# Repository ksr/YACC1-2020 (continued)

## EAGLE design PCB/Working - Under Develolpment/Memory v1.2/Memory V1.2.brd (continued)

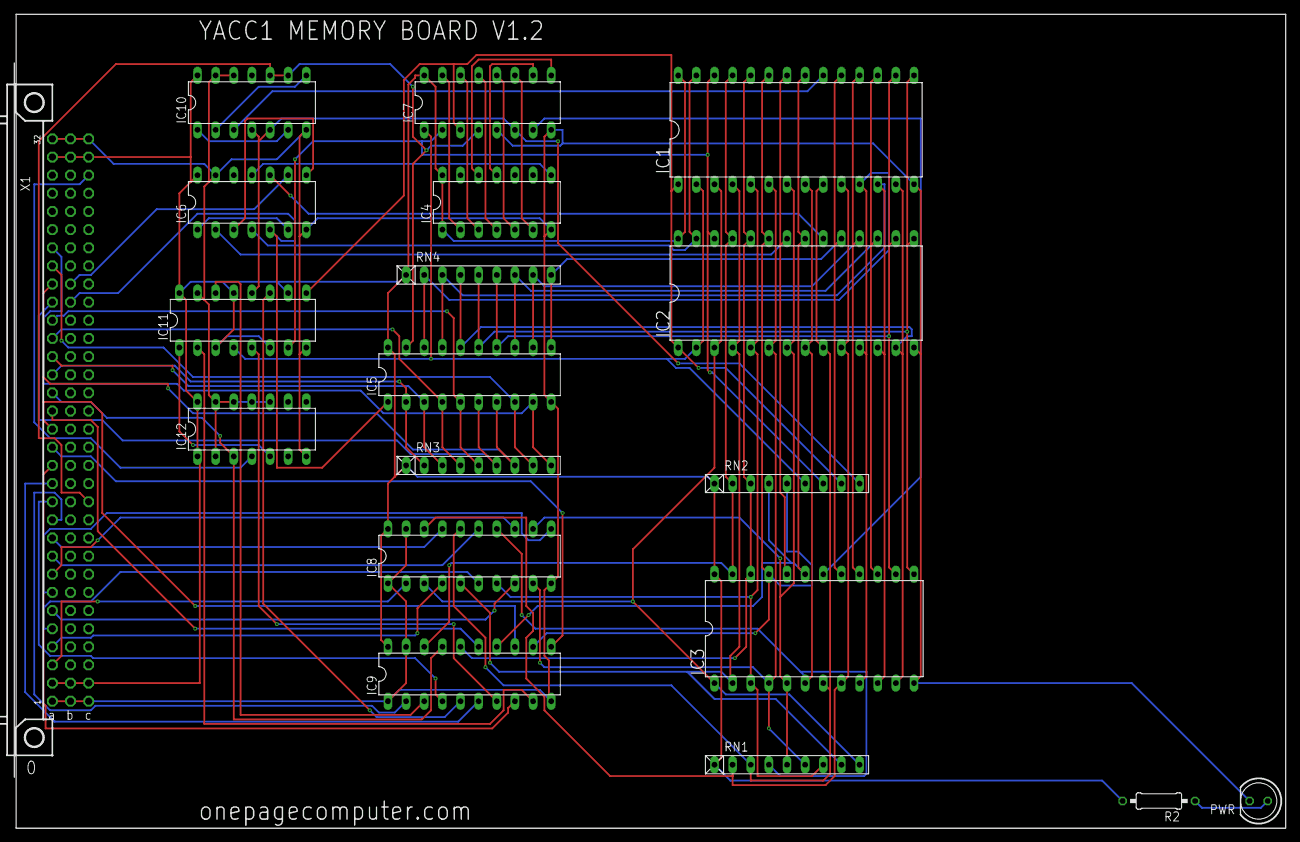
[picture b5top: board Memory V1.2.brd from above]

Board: 2 copper layers, 177.8 x 114.0 mm, 19 parts (0 on the bottom side), 77 nets.

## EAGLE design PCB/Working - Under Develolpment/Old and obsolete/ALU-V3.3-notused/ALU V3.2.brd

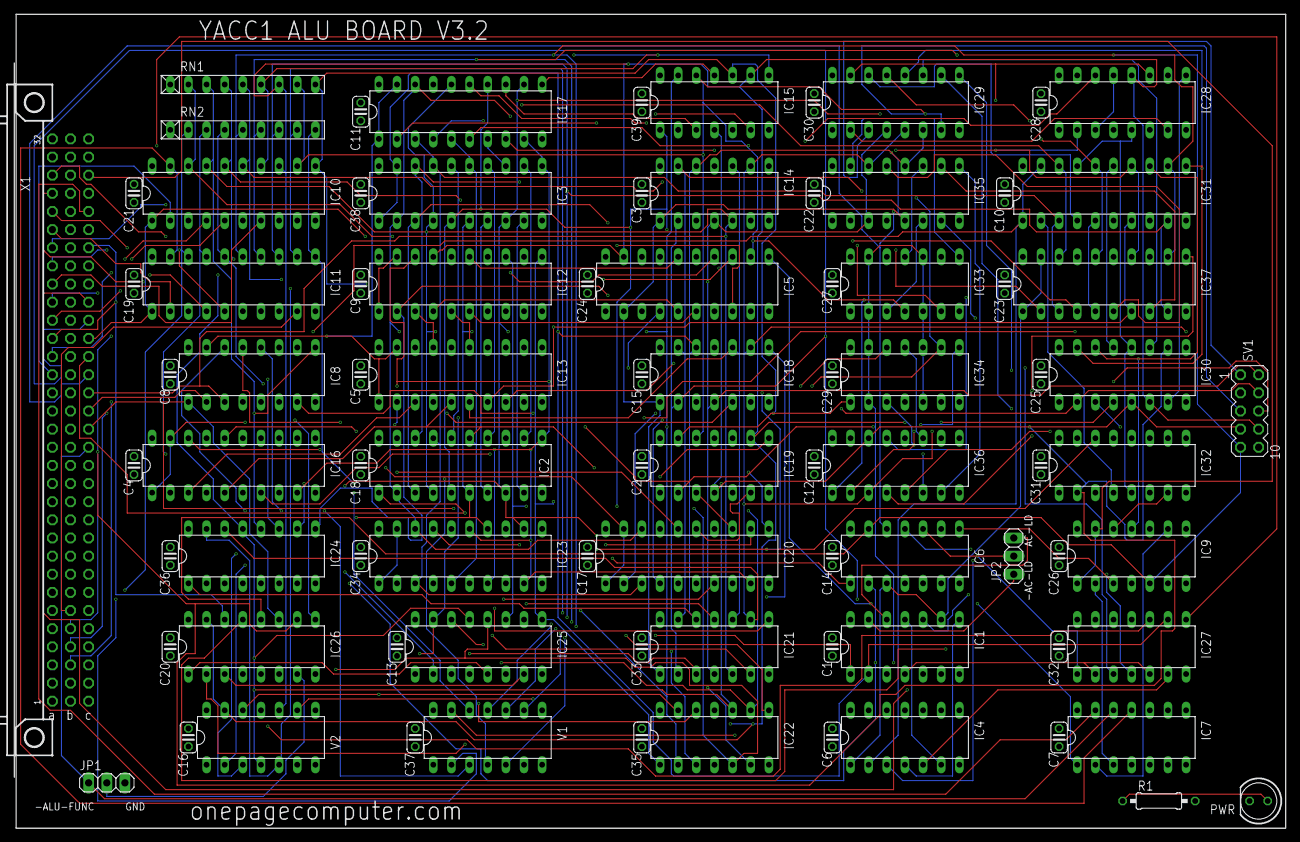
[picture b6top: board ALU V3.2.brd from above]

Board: 4 copper layers, 177.8 x 114.0 mm, 86 parts (0 on the bottom side), 162 nets.

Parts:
C1, C2, C3, C4, C5, C6, C7, C8, C9, C10, C11, C12, C13, C14, C15, C16, C17, C18, C19, C20, C22, C23, C24, C25, C26, C27, C28, C29, C30, C31, C32, C33, C34, C35, C36, C37, C38, C39: .1uf; C025-024X044
C21: ,1uf; C025-024X044
IC1: 74ALS04N; DIL14
IC2: 74LS240N; DIL20
IC3, IC12, IC13, IC16, IC17, IC20, IC23, IC31, IC37: 74LS244N; DIL20
IC4: 74LS00N; DIL14
IC5: 74LS374N; DIL20
IC6: 74ALS08N; DIL14
IC7, IC21, IC22: 74LS32N; DIL14
IC8: 74LS138N; DIL16
IC9: 74LS74N; DIL14
IC10, IC11: 74LS245N; DIL20
IC14, IC15, IC27, IC33, IC34: 74LS86N; DIL14
IC18, IC19: 74LS08N; DIL14
IC24, IC25: 74LS85N; DIL16
IC26: 74LS251N; DIL16
IC28, IC32: 74LS153N; DIL16
IC29, IC30: 74LS194N; DIL16
IC35, IC36: 74LS283N; DIL16
JP1, JP2: 1X03
PWR: LED5MM
R1: 330; 0207/10
RN1, RN2: 10k; RN-9
SV1: MA05-2
V1, V2: 744078N; DIL14
X1: FABC96R

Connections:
-AC-LD: IC1.13, JP2.1, X1.C22
-AC-LD-INV: IC1.1, IC2.1, IC2.19, X1.C20
-AC-RD: IC10.1, IC11.1, IC12.1, IC12.19, X1.C21
-ADD: IC6.1, IC8.7
-ADD/SUB: IC1.9, IC4.1, IC6.3, IC37.1, IC37.19
-ALU-FUNC: IC7.12, JP1.1, X1.C15
-ALU-IO-EN: IC7.11, IC10.19, IC11.19
-AND: IC8.13, IC20.1, IC20.19
-BUS-EN: IC7.13, X1.C28
-DATA: IC8.15, IC13.1, IC13.19
-OR: IC8.12, IC23.1, IC23.19
-RESET: IC9.1, IC9.13, X1.C30
-SHIFT: IC4.2, IC8.10, IC31.1, IC31.19
-SR-LD: IC1.5, X1.C23
-SUB: IC1.3, IC6.2, IC8.14
-XOR: IC8.11, IC17.1, IC17.19
-ZERO: IC8.9, IC16.1, IC16.19
AC-LD: IC1.12, IC5.11, JP2.3
AC-LD-INV: IC1.2, IC3.1, IC3.19, IC27.9
ACI-DATA0: IC2.18, IC3.18, IC5.3
ACI-DATA1: IC2.16, IC3.16, IC5.4
ACI-DATA2: IC2.14, IC3.14, IC5.7
ACI-DATA3: IC2.12, IC3.12, IC5.8
ACI-DATA4: IC2.9, IC3.9, IC5.13
ACI-DATA5: IC2.7, IC3.7, IC5.14
ACI-DATA6: IC2.5, IC3.5, IC5.17
ACI-DATA7: IC2.3, IC3.3, IC5.18
ACO-DATA0: IC5.2, IC12.2, IC14.1, IC18.1, IC21.1, IC24.9, IC29.3, IC35.5, SV1.1
ACO-DATA1: IC5.5, IC12.4, IC14.4, IC18.4, IC21.4, IC24.11, IC29.4, IC35.3, SV1.2
ACO-DATA2: IC5.6, IC12.6, IC14.9, IC18.9, IC21.9, IC24.14, IC29.5, IC35.14, SV1.3
ACO-DATA3: IC5.9, IC12.8, IC14.12, IC18.12, IC21.12, IC24.1, IC29.6, IC30.2, IC35.12, SV1.4
ACO-DATA4: IC5.12, IC12.11, IC15.12, IC19.12, IC22.1, IC25.9, IC29.7, IC30.3, IC36.5, SV1.5
ACO-DATA5: IC5.15, IC12.13, IC15.1, IC19.1, IC22.4, IC25.11, IC30.4, IC36.3, SV1.6
ACO-DATA6: IC5.16, IC12.15, IC15.4, IC19.4, IC22.9, IC25.14, IC30.5, IC36.14, SV1.7
ACO-DATA7: IC5.19, IC12.17, IC15.9, IC19.9, IC22.12, IC25.1, IC28.12, IC30.6, IC36.12, SV1.8
ALU0: IC8.1, IC26.11, IC29.9, IC30.9, IC32.14, X1.C16
ALU1: IC8.2, IC26.10, IC29.10, IC30.10, IC32.2, X1.C17
ALU2: IC8.3, IC26.9, IC28.14, X1.C18
ALU3: IC6.12, IC28.2, X1.C19
BDATA0: IC10.18, IC12.18, IC13.2, IC14.2, IC18.2, IC21.2, IC24.10, IC33.1, RN1.2, V2.2
BDATA1: IC10.17, IC12.16, IC13.4, IC14.5, IC18.5, IC21.5, IC24.12, IC33.4, RN1.3, V2.3
BDATA2: IC10.16, IC12.14, IC13.6, IC14.10, IC18.10, IC21.10, IC24.13, IC33.9, RN1.4, V2.4
BDATA3: IC10.15, IC12.12, IC13.8, IC14.13, IC18.13, IC21.13, IC24.15, IC33.12, RN1.5, V2.5
BDATA4: IC10.14, IC12.9, IC13.11, IC15.13, IC19.13, IC22.2, IC25.10, IC34.1, RN1.6, V2.9
BDATA5: IC10.13, IC12.7, IC13.13, IC15.2, IC19.2, IC22.5, IC25.12, IC34.4, RN1.7, V2.10
BDATA6: IC10.12, IC12.5, IC13.15, IC15.5, IC19.5, IC22.10, IC25.13, IC34.9, RN1.8, V2.11
BDATA7: IC10.11, IC12.3, IC13.17, IC15.10, IC19.10, IC22.13, IC25.15, IC34.12, RN1.9, V2.12
BDATA8: IC11.18, RN2.2, V1.2
BDATA9: IC11.17, RN2.3, V1.3
BDATA10: IC11.16, RN2.4, V1.4
BDATA11: IC11.15, RN2.5, V1.5
BDATA12: IC11.14, RN2.6, V1.9
BDATA13: IC11.13, RN2.7, V1.10
BDATA14: IC11.12, RN2.8, V1.11
BDATA15: IC11.11, RN2.9, V1.12
BR-COND: IC27.8, X1.C24
C/SHIFT: IC6.13, IC9.5, IC26.12, IC28.3, IC28.13, SV1.9
CO/BO: IC1.10, IC7.1
DATA0: IC10.2, X1.A19
DATA1: IC10.3, X1.A20
DATA2: IC10.4, X1.A21
DATA3: IC10.5, X1.A22
DATA4: IC10.6, X1.A23
DATA5: IC10.7, X1.A24
DATA6: IC10.8, X1.A25
DATA7: IC10.9, X1.A26
DATA8: IC11.2, X1.A27
DATA9: IC11.3, X1.A28
DATA10: IC11.4, X1.A29
DATA11: IC11.5, X1.A30
DATA12: IC11.6, X1.B3
DATA13: IC11.7, X1.B4
DATA14: IC11.8, X1.B5
DATA15: IC11.9, X1.B6
GND: C1.2, C2.2, C3.2, C4.2, C5.2, C6.2, C7.2, C8.2, C9.2, C10.2, C11.2, C12.2, C13.2, C14.2, C15.2, C16.2, C17.2, C18.2, C19.2, C20.2, C21.2, C22.2, C23.2, C24.2, C25.2, C26.2, C27.2, C28.2, C29.2, C30.2, C31.2, C32.2, C33.2, C34.2, C35.2, C36.2, C37.2, C38.2, C39.2, IC1.7, IC2.10, IC3.10, IC4.7, IC4.9, IC4.10, IC4.12, IC4.13, IC5.1, IC5.10, IC6.7, IC7.4, IC7.5, IC7.7, IC7.9, IC7.10, IC8.4, IC8.5, IC8.8, IC9.7, IC10.10, IC11.10, IC12.10, IC13.10, IC14.7, IC15.7, IC16.2, IC16.4, IC16.6, IC16.8, IC16.10, IC16.11, IC16.13, IC16.15, IC16.17, IC17.10, IC18.7, IC19.7, IC20.10, IC21.7, IC22.7, IC23.10, IC24.2, IC24.4, IC24.8, IC25.8, IC26.8, IC27.7, IC27.12, IC27.13, IC28.1, IC28.4, IC28.6, IC28.8, IC28.10, IC28.15, IC29.8, IC30.8, IC31.10, IC32.1, IC32.3, IC32.6, IC32.8, IC32.10, IC32.11, IC32.12, IC32.13, IC32.15, IC33.7, IC34.7, IC35.8, IC36.8, IC37.10, JP1.3, PWR.K, SV1.10, V1.7, V2.7, X1.A1, X1.A32, X1.B1, X1.B32, X1.C1, X1.C32
IN: IC26.14, X1.C26
INV-IN0: IC2.2, IC3.2, IC13.18, IC16.18, IC17.18, IC20.18, IC23.18, IC31.18, IC37.18
INV-IN1: IC2.4, IC3.4, IC13.16, IC16.16, IC17.16, IC20.16, IC23.16, IC31.16, IC37.16
INV-IN2: IC2.6, IC3.6, IC13.14, IC16.14, IC17.14, IC20.14, IC23.14, IC31.14, IC37.14
INV-IN3: IC2.8, IC3.8, IC13.12, IC16.12, IC17.12, IC20.12, IC23.12, IC31.12, IC37.12
INV-IN4: IC2.11, IC3.11, IC13.9, IC16.9, IC17.9, IC20.9, IC23.9, IC31.9, IC37.9
INV-IN5: IC2.13, IC3.13, IC13.7, IC16.7, IC17.7, IC20.7, IC23.7, IC31.7, IC37.7
INV-IN6: IC2.15, IC3.15, IC13.5, IC16.5, IC17.5, IC20.5, IC23.5, IC31.5, IC37.5
INV-IN7: IC2.17, IC3.17, IC13.3, IC16.3, IC17.3, IC20.3, IC23.3, IC31.3, IC37.3
unnamed: IC27.4, IC36.9
unnamed: IC27.3, IC35.7
unnamed: IC4.3, IC6.9
unnamed: IC26.7, JP1.2
unnamed: IC6.8, IC9.3
unnamed: IC6.4, IC26.15, V2.13
unnamed: IC7.3, IC9.2
unnamed: IC6.11, IC27.1
unnamed: IC6.10, JP2.2
unnamed: IC4.5, IC27.6
unnamed: IC9.12, IC32.7
unnamed: IC33.6, IC35.2
unnamed: IC34.6, IC36.2
unnamed: PWR.A, R1.1
unnamed: IC1.8, IC4.4
unnamed: IC1.11, IC4.6
unnamed: IC33.8, IC35.15
unnamed: IC33.11, IC35.11
unnamed: IC33.3, IC35.6
unnamed: IC34.3, IC36.6
unnamed: IC34.8, IC36.15
unnamed: IC34.11, IC36.11
unnamed: IC35.4, IC37.2
unnamed: IC35.1, IC37.4
unnamed: IC35.13, IC37.6
unnamed: IC35.10, IC37.8
unnamed: IC36.4, IC37.11
unnamed: IC36.1, IC37.13
unnamed: IC36.13, IC37.15
unnamed: IC36.10, IC37.17
unnamed: IC35.9, IC36.7
unnamed: IC24.5, IC25.4
unnamed: IC24.6, IC25.3
unnamed: IC24.7, IC25.2
unnamed: IC25.7, IC26.3
unnamed: IC25.6, IC26.2
unnamed: IC25.5, IC26.1
unnamed: IC6.5, V1.13
unnamed: IC6.6, IC26.13
unnamed: IC26.5, IC27.10
unnamed: IC29.14, IC31.4
unnamed: IC29.13, IC31.6
unnamed: IC29.12, IC31.8
unnamed: IC30.15, IC31.11
unnamed: IC30.14, IC31.13
unnamed: IC30.13, IC31.15
unnamed: IC28.7, IC29.2
unnamed: IC28.9, IC30.7
unnamed: IC21.3, IC23.2
unnamed: IC21.6, IC23.4
unnamed: IC21.8, IC23.6
unnamed: IC21.11, IC23.8
unnamed: IC22.3, IC23.11
unnamed: IC22.6, IC23.13
unnamed: IC22.8, IC23.15
unnamed: IC22.11, IC23.17
unnamed: IC18.3, IC20.2
unnamed: IC18.6, IC20.4
unnamed: IC18.8, IC20.6
unnamed: IC18.11, IC20.8
unnamed: IC19.11, IC20.11
unnamed: IC19.3, IC20.13
unnamed: IC19.6, IC20.15
unnamed: IC19.8, IC20.17
unnamed: IC14.3, IC17.2
unnamed: IC14.6, IC17.4
unnamed: IC14.8, IC17.6
unnamed: IC14.11, IC17.8
unnamed: IC15.11, IC17.11
unnamed: IC15.3, IC17.13
unnamed: IC15.6, IC17.15
unnamed: IC15.8, IC17.17
SHIFT-OUT: IC7.2, IC9.9
SR-LD: IC1.6, IC9.11, IC29.11, IC30.11
SRD0: IC28.11, IC29.15, IC31.2, IC32.4
SRD7: IC28.5, IC30.12, IC31.17, IC32.5
SUB: IC1.4, IC27.2, IC27.5, IC33.2, IC33.5, IC33.10, IC33.13, IC34.2, IC34.5, IC34.10, IC34.13
VCC: C1.1, C2.1, C3.1, C4.1, C5.1, C6.1, C7.1, C8.1, C9.1, C10.1, C11.1, C12.1, C13.1, C14.1, C15.1, C16.1, C17.1, C18.1, C19.1, C20.1, C21.1, C22.1, C23.1, C24.1, C25.1, C26.1, C27.1, C28.1, C29.1, C30.1, C31.1, C32.1, C33.1, C34.1, C35.1, C36.1, C37.1, C38.1, C39.1, IC1.14, IC2.20, IC3.20, IC4.14, IC5.20, IC6.14, IC7.14, IC8.6, IC8.16, IC9.4, IC9.10, IC9.14, IC10.20, IC11.20, IC12.20, IC13.20, IC14.14, IC15.14, IC16.20, IC17.20, IC18.14, IC19.14, IC20.20, IC21.14, IC22.14, IC23.20, IC24.3, IC24.16, IC25.16, IC26.4, IC26.16, IC27.14, IC28.16, IC29.1, IC29.16, IC30.1, IC30.16, IC31.20, IC32.16, IC33.14, IC34.14, IC35.16, IC36.16, IC37.20, R1.2, RN1.1, RN2.1, V1.14, V2.14, X1.A2, X1.A31, X1.B2, X1.B31, X1.C2, X1.C31

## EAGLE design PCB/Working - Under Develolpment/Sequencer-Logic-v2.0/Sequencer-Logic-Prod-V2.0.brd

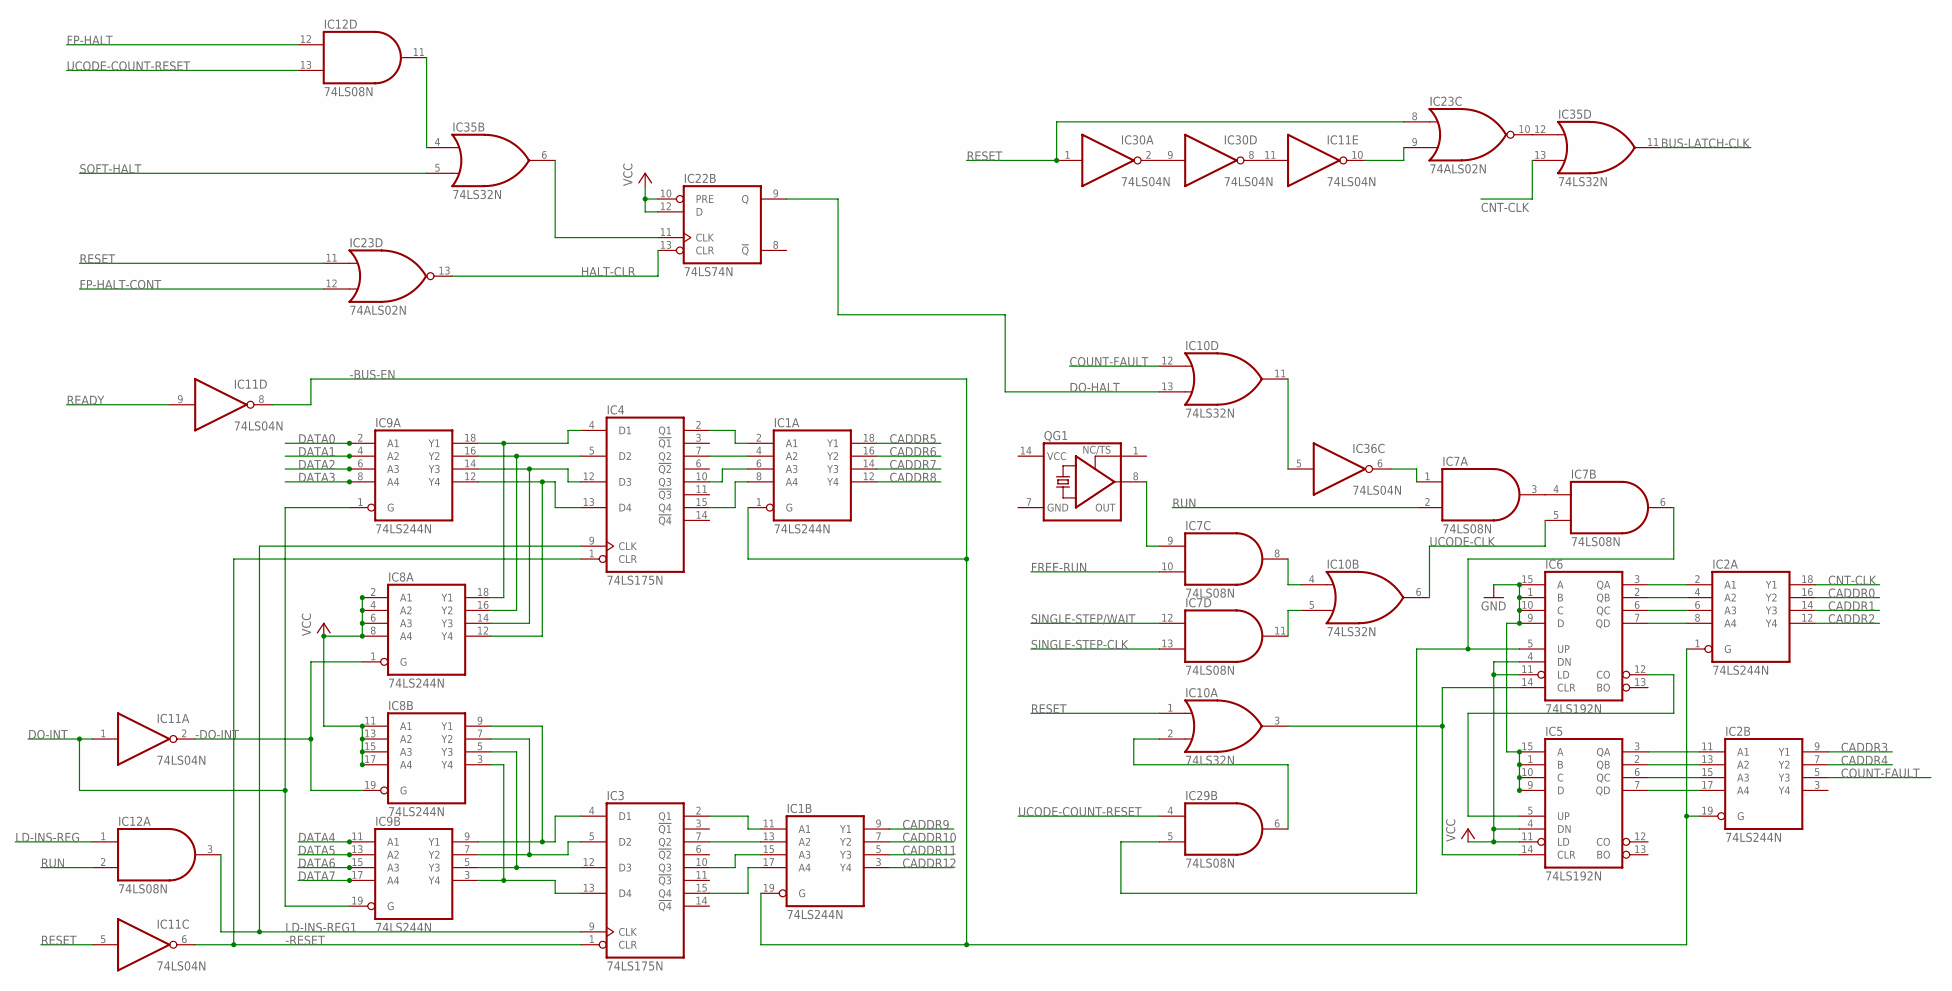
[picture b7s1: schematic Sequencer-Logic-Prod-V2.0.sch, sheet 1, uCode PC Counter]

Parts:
IC1, IC2, IC8, IC9: 74LS244N; DIL20
IC3, IC4: 74LS175N; DIL16
IC5, IC6: 74LS192N; DIL16
IC7, IC12, IC29: 74LS08N; DIL14
IC10, IC35: 74LS32N; DIL14
IC11, IC30, IC36: 74LS04N; DIL14
IC22: 74LS74N; DIL14
IC23: 74ALS02N; DIL14
QG1: XO-14; DIL14S

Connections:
-BUS-EN: IC1.1 (G), IC1.19 (G), IC2.1 (G), IC2.19 (G), IC11.8 (O); also elsewhere on the board
-DO-INT: IC8.1 (G), IC8.19 (G), IC11.2 (O)
-RESET: IC3.1 (CLR), IC4.1 (CLR), IC11.6 (O); also elsewhere on the board
BUS-LATCH-CLK: IC35.11 (O); also elsewhere on the board
CADDR0: IC2.16 (Y2); also elsewhere on the board
CADDR1: IC2.14 (Y3); also elsewhere on the board
CADDR2: IC2.12 (Y4); also elsewhere on the board
CADDR3: IC2.9 (Y1); also elsewhere on the board
CADDR4: IC2.7 (Y2); also elsewhere on the board
CADDR5: IC1.18 (Y1); also elsewhere on the board
CADDR6: IC1.16 (Y2); also elsewhere on the board
CADDR7: IC1.14 (Y3); also elsewhere on the board
CADDR8: IC1.12 (Y4); also elsewhere on the board
CADDR9: IC1.9 (Y1); also elsewhere on the board
CADDR10: IC1.7 (Y2); also elsewhere on the board
CADDR11: IC1.5 (Y3); also elsewhere on the board
CADDR12: IC1.3 (Y4); also elsewhere on the board
CNT-CLK: IC2.18 (Y1), IC35.13 (I1)
COUNT-FAULT: IC2.5 (Y3), IC10.12 (I0)
COUNT-RESET: IC5.14 (CLR), IC6.14 (CLR), IC10.3 (O)
DATA0: IC9.2 (A1); also elsewhere on the board
DATA1: IC9.4 (A2); also elsewhere on the board
DATA2: IC9.6 (A3); also elsewhere on the board
DATA3: IC9.8 (A4); also elsewhere on the board
DATA4: IC9.11 (A1); also elsewhere on the board
DATA5: IC9.13 (A2); also elsewhere on the board
DATA6: IC9.15 (A3); also elsewhere on the board
DATA7: IC9.17 (A4); also elsewhere on the board
DO-HALT: IC10.13 (I1), IC22.9 (Q)
DO-INT: IC9.1 (G), IC9.19 (G), IC11.1 (I); also elsewhere on the board
FP-HALT: IC12.12 (I0); also elsewhere on the board
FP-HALT-CONT: IC23.12 (I1); also elsewhere on the board
FREE-RUN: IC7.10 (I1); also elsewhere on the board
GND: IC1.10 (GND), IC2.10 (GND), IC3.8 (GND), IC4.8 (GND), IC5.1 (B), IC5.8 (GND), IC5.9 (D), IC5.10 (C), IC5.15 (A), IC6.1 (B), IC6.8 (GND), IC6.9 (D), IC6.10 (C), IC6.15 (A), IC7.7 (GND), IC8.10 (GND), IC9.10 (GND), IC10.7 (GND), IC11.7 (GND), IC12.7 (GND), IC22.7 (GND), IC23.7 (GND), IC29.7 (GND), IC30.7 (GND), IC35.7 (GND), IC36.7 (GND), QG1.7 (GND); also elsewhere on the board
HALT-CLR: IC22.13 (CLR), IC23.13 (O)
LD-INS-REG: IC12.1 (I0); also elsewhere on the board
LD-INS-REG1: IC3.9 (CLK), IC4.9 (CLK), IC12.3 (O)
unnamed: IC5.5 (UP), IC6.12 (CO)
unnamed: IC1.2 (A1), IC4.2 (Q1)
unnamed: IC1.4 (A2), IC4.7 (Q2)
unnamed: IC6.5 (UP), IC7.6 (O), IC29.5 (I1)
unnamed: IC4.4 (D1), IC8.18 (Y1), IC9.18 (Y1)
unnamed: IC4.5 (D2), IC8.16 (Y2), IC9.16 (Y2)
unnamed: IC2.2 (A1), IC6.3 (QA)
unnamed: IC2.4 (A2), IC6.2 (QB)
unnamed: IC2.6 (A3), IC6.6 (QC)
unnamed: IC1.6 (A3), IC4.10 (Q3)
unnamed: IC2.8 (A4), IC6.7 (QD)
unnamed: IC2.11 (A1), IC5.3 (QA)
unnamed: IC2.13 (A2), IC5.2 (QB)
unnamed: IC2.15 (A3), IC5.6 (QC)
unnamed: IC2.17 (A4), IC5.7 (QD)
unnamed: IC7.1 (I0), IC36.6 (O)
unnamed: IC4.12 (D3), IC8.14 (Y3), IC9.14 (Y3)
unnamed: IC4.13 (D4), IC8.12 (Y4), IC9.12 (Y4)
unnamed: IC3.4 (D1), IC8.9 (Y1), IC9.9 (Y1)
unnamed: IC3.5 (D2), IC8.7 (Y2), IC9.7 (Y2)
unnamed: IC3.12 (D3), IC8.5 (Y3), IC9.5 (Y3)
unnamed: IC3.13 (D4), IC8.3 (Y4), IC9.3 (Y4)
unnamed: IC1.8 (A4), IC4.15 (Q4)
unnamed: IC10.11 (O), IC36.5 (I)
unnamed: IC7.3 (O), IC7.4 (I0)
unnamed: IC23.10 (O), IC35.12 (I0)
unnamed: IC22.11 (CLK), IC35.6 (O)
unnamed: IC1.11 (A1), IC3.2 (Q1)
unnamed: IC1.13 (A2), IC3.7 (Q2)
unnamed: IC1.15 (A3), IC3.10 (Q3)
unnamed: IC1.17 (A4), IC3.15 (Q4)
unnamed: IC7.11 (O), IC10.5 (I1)
unnamed: IC7.8 (O), IC10.4 (I0)
unnamed: IC7.9 (I0), QG1.8 (OUT)
unnamed: IC11.11 (I), IC30.8 (O)
unnamed: IC30.2 (O), IC30.9 (I)
unnamed: IC11.10 (O), IC23.9 (I1)
unnamed: IC12.11 (O), IC35.4 (I0)
unnamed: IC10.2 (I1), IC29.6 (O)
READY: IC11.9 (I); also elsewhere on the board
RESET: IC10.1 (I0), IC11.5 (I), IC23.8 (I0), IC23.11 (I0), IC30.1 (I); also elsewhere on the board
RUN: IC7.2 (I1), IC12.2 (I1); also elsewhere on the board
SINGLE-STEP-CLK: IC7.13 (I1); also elsewhere on the board
SINGLE-STEP/WAIT: IC7.12 (I0); also elsewhere on the board
SOFT-HALT: IC35.5 (I1); also elsewhere on the board
UCODE-CLK: IC7.5 (I1), IC10.6 (O)
UCODE-COUNT-RESET: IC12.13 (I1), IC29.4 (I0); also elsewhere on the board
VCC: IC1.20 (VCC), IC2.20 (VCC), IC3.16 (VCC), IC4.16 (VCC), IC5.4 (DN), IC5.11 (LD), IC5.16 (VCC), IC6.4 (DN), IC6.11 (LD), IC6.16 (VCC), IC7.14 (VCC), IC8.2 (A1), IC8.4 (A2), IC8.6 (A3), IC8.8 (A4), IC8.11 (A1), IC8.13 (A2), IC8.15 (A3), IC8.17 (A4), IC8.20 (VCC), IC9.20 (VCC), IC10.14 (VCC), IC11.14 (VCC), IC12.14 (VCC), IC22.10 (PRE), IC22.12 (D), IC22.14 (VCC), IC23.14 (VCC), IC29.14 (VCC), IC30.14 (VCC), IC35.14 (VCC), IC36.14 (VCC), QG1.14 (VCC); also elsewhere on the board

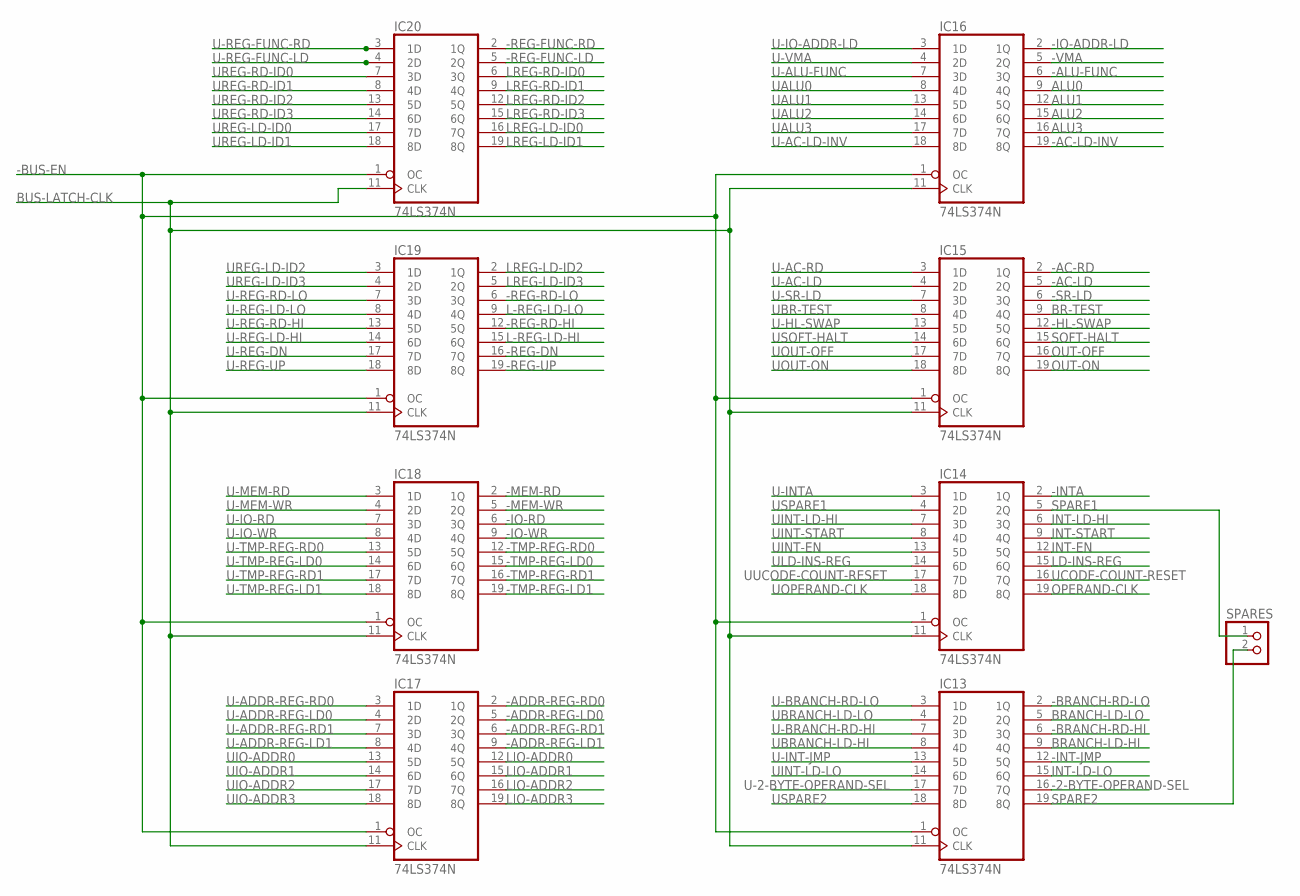
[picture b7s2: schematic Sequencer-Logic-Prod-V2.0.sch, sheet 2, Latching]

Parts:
IC13, IC14, IC15, IC16, IC17, IC18, IC19, IC20: 74LS374N; DIL20
SPARES: PINHD-1X2; 1X02

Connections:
-2-BYTE-OPERAND-SEL: IC13.16 (7Q); also elsewhere on the board
-AC-LD: IC15.5 (2Q); also elsewhere on the board
-AC-LD-INV: IC16.19 (8Q); also elsewhere on the board
-AC-RD: IC15.2 (1Q); also elsewhere on the board
-ADDR-REG-LD0: IC17.5 (2Q); also elsewhere on the board
-ADDR-REG-LD1: IC17.9 (4Q); also elsewhere on the board
-ADDR-REG-RD0: IC17.2 (1Q); also elsewhere on the board
-ADDR-REG-RD1: IC17.6 (3Q); also elsewhere on the board
-ALU-FUNC: IC16.6 (3Q); also elsewhere on the board
-BRANCH-RD-HI: IC13.6 (3Q); also elsewhere on the board
-BRANCH-RD-LO: IC13.2 (1Q); also elsewhere on the board
-BUS-EN: IC13.1 (OC), IC14.1 (OC), IC15.1 (OC), IC16.1 (OC), IC17.1 (OC), IC18.1 (OC), IC19.1 (OC), IC20.1 (OC); also elsewhere on the board
-HL-SWAP: IC15.12 (5Q); also elsewhere on the board
-INT-JMP: IC13.12 (5Q); also elsewhere on the board
-INTA: IC14.2 (1Q); also elsewhere on the board
-IO-ADDR-LD: IC16.2 (1Q); also elsewhere on the board
-IO-RD: IC18.6 (3Q); also elsewhere on the board
-IO-WR: IC18.9 (4Q); also elsewhere on the board
-MEM-RD: IC18.2 (1Q); also elsewhere on the board
-MEM-WR: IC18.5 (2Q); also elsewhere on the board
-REG-DN: IC19.16 (7Q); also elsewhere on the board
-REG-FUNC-LD: IC20.5 (2Q); also elsewhere on the board
-REG-FUNC-RD: IC20.2 (1Q); also elsewhere on the board
-REG-RD-HI: IC19.12 (5Q); also elsewhere on the board
-REG-RD-LO: IC19.6 (3Q); also elsewhere on the board
-REG-UP: IC19.19 (8Q); also elsewhere on the board
-SR-LD: IC15.6 (3Q); also elsewhere on the board
-TMP-REG-LD0: IC18.15 (6Q); also elsewhere on the board
-TMP-REG-LD1: IC18.19 (8Q); also elsewhere on the board
-TMP-REG-RD0: IC18.12 (5Q); also elsewhere on the board
-TMP-REG-RD1: IC18.16 (7Q); also elsewhere on the board
-VMA: IC16.5 (2Q); also elsewhere on the board
ALU0: IC16.9 (4Q); also elsewhere on the board
ALU1: IC16.12 (5Q); also elsewhere on the board
ALU2: IC16.15 (6Q); also elsewhere on the board
ALU3: IC16.16 (7Q); also elsewhere on the board
BR-TEST: IC15.9 (4Q); also elsewhere on the board
BRANCH-LD-HI: IC13.9 (4Q); also elsewhere on the board
BRANCH-LD-LO: IC13.5 (2Q); also elsewhere on the board
BUS-LATCH-CLK: IC13.11 (CLK), IC14.11 (CLK), IC15.11 (CLK), IC16.11 (CLK), IC17.11 (CLK), IC18.11 (CLK), IC19.11 (CLK), IC20.11 (CLK); also elsewhere on the board
GND: IC13.10 (GND), IC14.10 (GND), IC15.10 (GND), IC16.10 (GND), IC17.10 (GND), IC18.10 (GND), IC19.10 (GND), IC20.10 (GND); also elsewhere on the board
INT-EN: IC14.12 (5Q); also elsewhere on the board
INT-LD-HI: IC14.6 (3Q); also elsewhere on the board
INT-LD-LO: IC13.15 (6Q); also elsewhere on the board
INT-START: IC14.9 (4Q); also elsewhere on the board
L-REG-LD-HI: IC19.15 (6Q); also elsewhere on the board
L-REG-LD-LO: IC19.9 (4Q); also elsewhere on the board
LD-INS-REG: IC14.15 (6Q); also elsewhere on the board
LIO-ADDR0: IC17.12 (5Q); also elsewhere on the board
LIO-ADDR1: IC17.15 (6Q); also elsewhere on the board
LIO-ADDR2: IC17.16 (7Q); also elsewhere on the board
LIO-ADDR3: IC17.19 (8Q); also elsewhere on the board
LREG-LD-ID0: IC20.16 (7Q); also elsewhere on the board
LREG-LD-ID1: IC20.19 (8Q); also elsewhere on the board
LREG-LD-ID2: IC19.2 (1Q); also elsewhere on the board
LREG-LD-ID3: IC19.5 (2Q); also elsewhere on the board
LREG-RD-ID0: IC20.6 (3Q); also elsewhere on the board
LREG-RD-ID1: IC20.9 (4Q); also elsewhere on the board
LREG-RD-ID2: IC20.12 (5Q); also elsewhere on the board
LREG-RD-ID3: IC20.15 (6Q); also elsewhere on the board
OPERAND-CLK: IC14.19 (8Q); also elsewhere on the board
OUT-OFF: IC15.16 (7Q); also elsewhere on the board
OUT-ON: IC15.19 (8Q); also elsewhere on the board
SOFT-HALT: IC15.15 (6Q); also elsewhere on the board
SPARE1: IC14.5 (2Q), SPARES.1
SPARE2: IC13.19 (8Q), SPARES.2
U-2-BYTE-OPERAND-SEL: IC13.17 (7D); also elsewhere on the board
U-AC-LD: IC15.4 (2D); also elsewhere on the board
U-AC-LD-INV: IC16.18 (8D); also elsewhere on the board
U-AC-RD: IC15.3 (1D); also elsewhere on the board
U-ADDR-REG-LD0: IC17.4 (2D); also elsewhere on the board
U-ADDR-REG-LD1: IC17.8 (4D); also elsewhere on the board
U-ADDR-REG-RD0: IC17.3 (1D); also elsewhere on the board
U-ADDR-REG-RD1: IC17.7 (3D); also elsewhere on the board
U-ALU-FUNC: IC16.7 (3D); also elsewhere on the board
U-BRANCH-RD-HI: IC13.7 (3D); also elsewhere on the board
U-BRANCH-RD-LO: IC13.3 (1D); also elsewhere on the board
U-HL-SWAP: IC15.13 (5D); also elsewhere on the board
U-INT-JMP: IC13.13 (5D); also elsewhere on the board
U-INTA: IC14.3 (1D); also elsewhere on the board
U-IO-ADDR-LD: IC16.3 (1D); also elsewhere on the board
U-IO-RD: IC18.7 (3D); also elsewhere on the board
U-IO-WR: IC18.8 (4D); also elsewhere on the board
U-MEM-RD: IC18.3 (1D); also elsewhere on the board
U-MEM-WR: IC18.4 (2D); also elsewhere on the board
U-REG-DN: IC19.17 (7D); also elsewhere on the board
U-REG-FUNC-LD: IC20.4 (2D); also elsewhere on the board
U-REG-FUNC-RD: IC20.3 (1D); also elsewhere on the board
U-REG-LD-HI: IC19.14 (6D); also elsewhere on the board
U-REG-LD-LO: IC19.8 (4D); also elsewhere on the board
U-REG-RD-HI: IC19.13 (5D); also elsewhere on the board
U-REG-RD-LO: IC19.7 (3D); also elsewhere on the board
U-REG-UP: IC19.18 (8D); also elsewhere on the board
U-SR-LD: IC15.7 (3D); also elsewhere on the board
U-TMP-REG-LD0: IC18.14 (6D); also elsewhere on the board
U-TMP-REG-LD1: IC18.18 (8D); also elsewhere on the board
U-TMP-REG-RD0: IC18.13 (5D); also elsewhere on the board
U-TMP-REG-RD1: IC18.17 (7D); also elsewhere on the board
U-VMA: IC16.4 (2D); also elsewhere on the board
UALU0: IC16.8 (4D); also elsewhere on the board
UALU1: IC16.13 (5D); also elsewhere on the board
UALU2: IC16.14 (6D); also elsewhere on the board
UALU3: IC16.17 (7D); also elsewhere on the board
UBR-TEST: IC15.8 (4D); also elsewhere on the board
UBRANCH-LD-HI: IC13.8 (4D); also elsewhere on the board
UBRANCH-LD-LO: IC13.4 (2D); also elsewhere on the board
UCODE-COUNT-RESET: IC14.16 (7Q); also elsewhere on the board
UINT-EN: IC14.13 (5D); also elsewhere on the board
UINT-LD-HI: IC14.7 (3D); also elsewhere on the board
UINT-LD-LO: IC13.14 (6D); also elsewhere on the board
UINT-START: IC14.8 (4D); also elsewhere on the board
UIO-ADDR0: IC17.13 (5D); also elsewhere on the board
UIO-ADDR1: IC17.14 (6D); also elsewhere on the board
UIO-ADDR2: IC17.17 (7D); also elsewhere on the board
UIO-ADDR3: IC17.18 (8D); also elsewhere on the board
ULD-INS-REG: IC14.14 (6D); also elsewhere on the board
UOPERAND-CLK: IC14.18 (8D); also elsewhere on the board
UOUT-OFF: IC15.17 (7D); also elsewhere on the board
UOUT-ON: IC15.18 (8D); also elsewhere on the board
UREG-LD-ID0: IC20.17 (7D); also elsewhere on the board
UREG-LD-ID1: IC20.18 (8D); also elsewhere on the board
UREG-LD-ID2: IC19.3 (1D); also elsewhere on the board
UREG-LD-ID3: IC19.4 (2D); also elsewhere on the board
UREG-RD-ID0: IC20.7 (3D); also elsewhere on the board
UREG-RD-ID1: IC20.8 (4D); also elsewhere on the board
UREG-RD-ID2: IC20.13 (5D); also elsewhere on the board
UREG-RD-ID3: IC20.14 (6D); also elsewhere on the board
USOFT-HALT: IC15.14 (6D)
USPARE1: IC14.4 (2D); also elsewhere on the board
USPARE2: IC13.18 (8D); also elsewhere on the board
UUCODE-COUNT-RESET: IC14.17 (7D); also elsewhere on the board
VCC: IC13.20 (VCC), IC14.20 (VCC), IC15.20 (VCC), IC16.20 (VCC), IC17.20 (VCC), IC18.20 (VCC), IC19.20 (VCC), IC20.20 (VCC); also elsewhere on the board

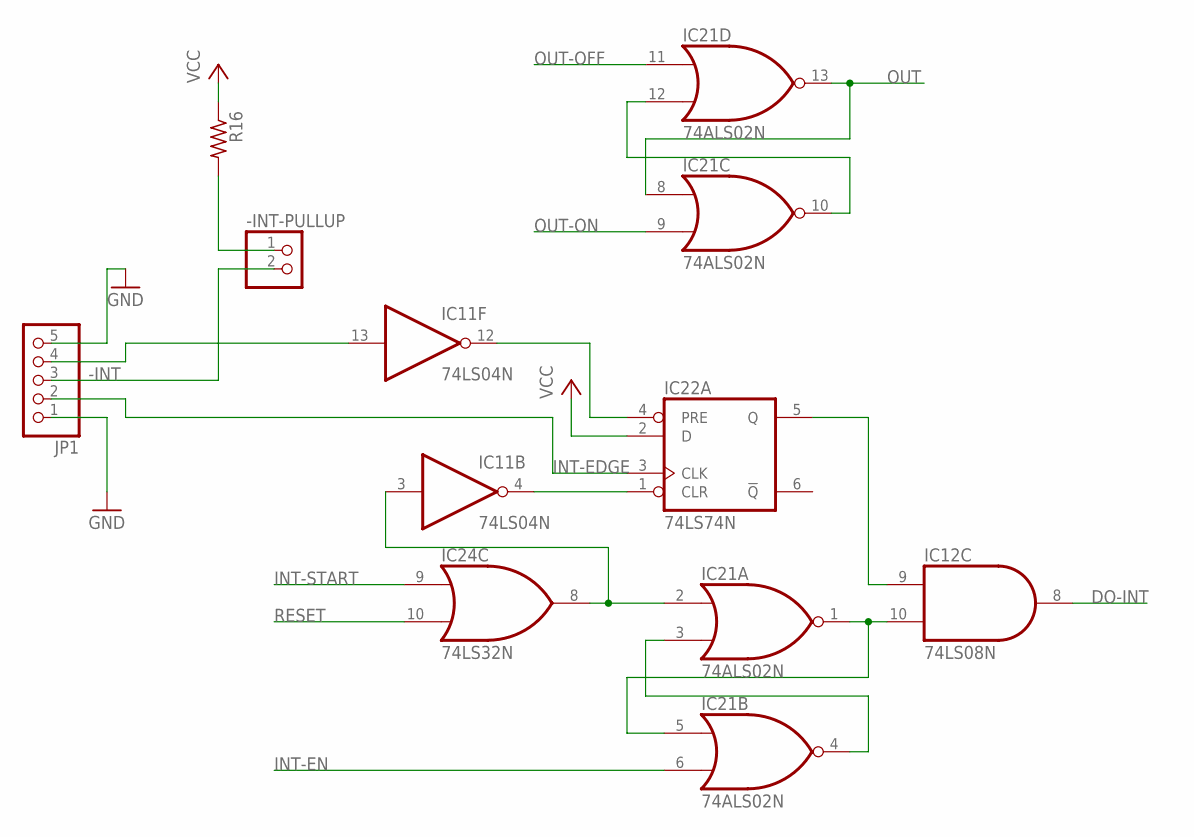
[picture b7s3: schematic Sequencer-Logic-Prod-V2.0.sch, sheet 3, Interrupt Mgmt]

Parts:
-INT-PULLUP: PINHD-1X2; 1X02
IC11: 74LS04N; DIL14
IC12: 74LS08N; DIL14
IC21: 74ALS02N; DIL14
IC22: 74LS74N; DIL14
IC24: 74LS32N; DIL14
JP1: PINHD-1X5; 1X05
R16: 10k; 0207/10

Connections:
-INT: -INT-PULLUP.2, JP1.3; also elsewhere on the board
DO-INT: IC12.8 (O); also elsewhere on the board
GND: IC11.7 (GND), IC12.7 (GND), IC21.7 (GND), IC22.7 (GND), IC24.7 (GND), JP1.1, JP1.5; also elsewhere on the board
INT-EDGE: IC22.3 (CLK), JP1.2
INT-EN: IC21.6 (I1); also elsewhere on the board
INT-START: IC24.9 (I0); also elsewhere on the board
unnamed: IC12.10 (I1), IC21.1 (O), IC21.5 (I0)
unnamed: IC21.3 (I1), IC21.4 (O)
unnamed: IC11.3 (I), IC21.2 (I0), IC24.8 (O)
unnamed: IC12.9 (I0), IC22.5 (Q)
unnamed: IC11.4 (O), IC22.1 (CLR)
unnamed: IC11.12 (O), IC22.4 (PRE)
unnamed: IC11.13 (I), JP1.4
unnamed: IC21.10 (O), IC21.12 (I1)
unnamed: -INT-PULLUP.1, R16.2
OUT: IC21.8 (I0), IC21.13 (O); also elsewhere on the board
OUT-OFF: IC21.11 (I0); also elsewhere on the board
OUT-ON: IC21.9 (I1); also elsewhere on the board
RESET: IC24.10 (I1); also elsewhere on the board
VCC: IC11.14 (VCC), IC12.14 (VCC), IC21.14 (VCC), IC22.2 (D), IC22.14 (VCC), IC24.14 (VCC), R16.1; also elsewhere on the board

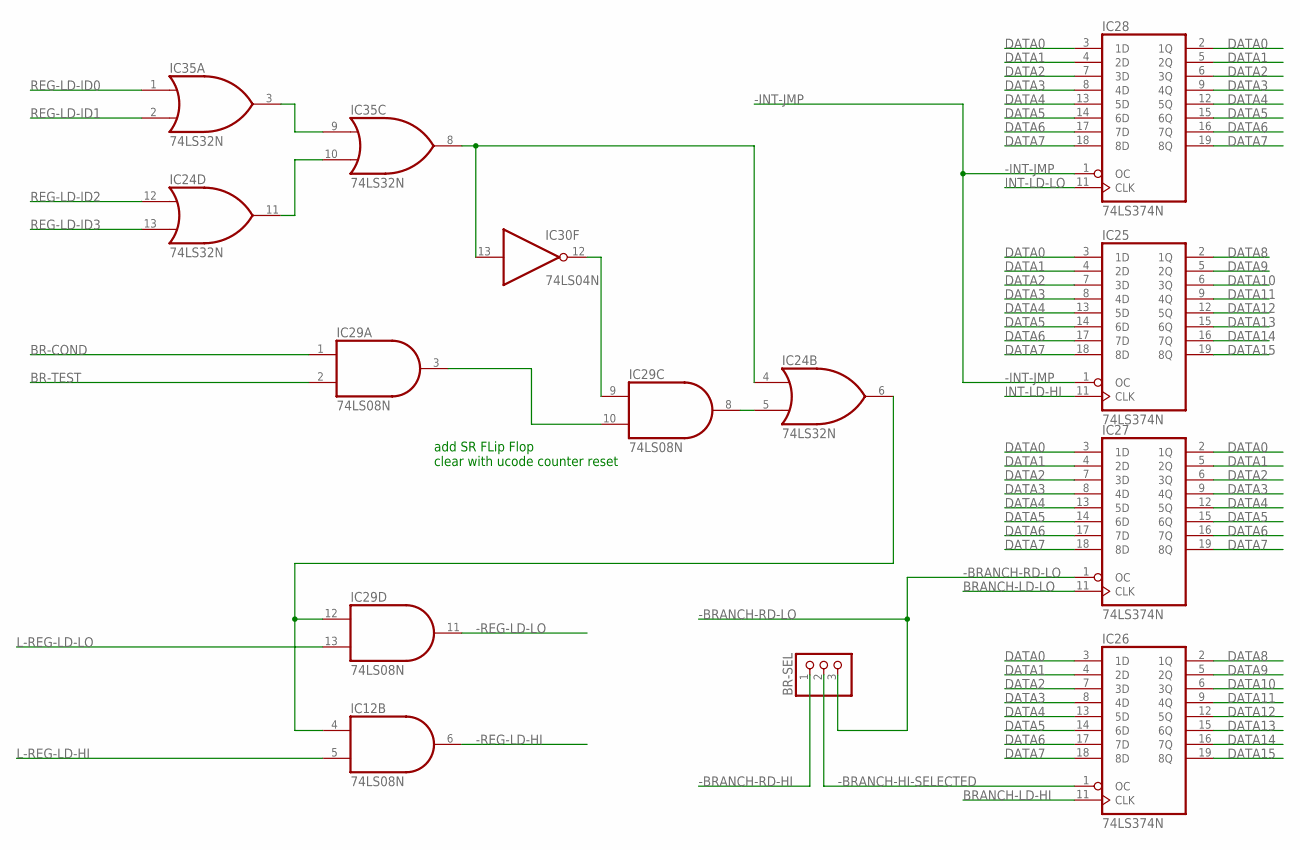
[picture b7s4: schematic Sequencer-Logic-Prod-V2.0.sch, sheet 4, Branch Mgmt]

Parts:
BR-SEL: PINHD-1X3; 1X03
IC12, IC29: 74LS08N; DIL14
IC24, IC35: 74LS32N; DIL14
IC25, IC26, IC27, IC28: 74LS374N; DIL20
IC30: 74LS04N; DIL14

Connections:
-BRANCH-HI-SELECTED: BR-SEL.2, IC26.1 (OC)
-BRANCH-RD-HI: BR-SEL.1; also elsewhere on the board
-BRANCH-RD-LO: BR-SEL.3, IC27.1 (OC); also elsewhere on the board
-INT-JMP: IC25.1 (OC), IC28.1 (OC); also elsewhere on the board
-REG-LD-HI: IC12.6 (O); also elsewhere on the board
-REG-LD-LO: IC29.11 (O); also elsewhere on the board
BR-COND: IC29.1 (I0); also elsewhere on the board
BR-TEST: IC29.2 (I1); also elsewhere on the board
BRANCH-LD-HI: IC26.11 (CLK); also elsewhere on the board
BRANCH-LD-LO: IC27.11 (CLK); also elsewhere on the board
DATA0: IC25.3 (1D), IC26.3 (1D), IC27.2 (1Q), IC27.3 (1D), IC28.2 (1Q), IC28.3 (1D); also elsewhere on the board
DATA1: IC25.4 (2D), IC26.4 (2D), IC27.4 (2D), IC27.5 (2Q), IC28.4 (2D), IC28.5 (2Q); also elsewhere on the board
DATA2: IC25.7 (3D), IC26.7 (3D), IC27.6 (3Q), IC27.7 (3D), IC28.6 (3Q), IC28.7 (3D); also elsewhere on the board
DATA3: IC25.8 (4D), IC26.8 (4D), IC27.8 (4D), IC27.9 (4Q), IC28.8 (4D), IC28.9 (4Q); also elsewhere on the board
DATA4: IC25.13 (5D), IC26.13 (5D), IC27.12 (5Q), IC27.13 (5D), IC28.12 (5Q), IC28.13 (5D); also elsewhere on the board
DATA5: IC25.14 (6D), IC26.14 (6D), IC27.14 (6D), IC27.15 (6Q), IC28.14 (6D), IC28.15 (6Q); also elsewhere on the board
DATA6: IC25.17 (7D), IC26.17 (7D), IC27.16 (7Q), IC27.17 (7D), IC28.16 (7Q), IC28.17 (7D); also elsewhere on the board
DATA7: IC25.18 (8D), IC26.18 (8D), IC27.18 (8D), IC27.19 (8Q), IC28.18 (8D), IC28.19 (8Q); also elsewhere on the board
DATA8: IC25.2 (1Q), IC26.2 (1Q); also elsewhere on the board
DATA9: IC25.5 (2Q), IC26.5 (2Q); also elsewhere on the board
DATA10: IC25.6 (3Q), IC26.6 (3Q); also elsewhere on the board
DATA11: IC25.9 (4Q), IC26.9 (4Q); also elsewhere on the board
DATA12: IC25.12 (5Q), IC26.12 (5Q); also elsewhere on the board
DATA13: IC25.15 (6Q), IC26.15 (6Q); also elsewhere on the board
DATA14: IC25.16 (7Q), IC26.16 (7Q); also elsewhere on the board
DATA15: IC25.19 (8Q), IC26.19 (8Q); also elsewhere on the board
GND: IC12.7 (GND), IC24.7 (GND), IC25.10 (GND), IC26.10 (GND), IC27.10 (GND), IC28.10 (GND), IC29.7 (GND), IC30.7 (GND), IC35.7 (GND); also elsewhere on the board
INT-LD-HI: IC25.11 (CLK); also elsewhere on the board
INT-LD-LO: IC28.11 (CLK); also elsewhere on the board
L-REG-LD-HI: IC12.5 (I1); also elsewhere on the board
L-REG-LD-LO: IC29.13 (I1); also elsewhere on the board
unnamed: IC35.3 (O), IC35.9 (I0)
unnamed: IC24.11 (O), IC35.10 (I1)
unnamed: IC29.3 (O), IC29.10 (I1)
unnamed: IC29.9 (I0), IC30.12 (O)
unnamed: IC24.5 (I1), IC29.8 (O)
unnamed: IC12.4 (I0), IC24.6 (O), IC29.12 (I0)
unnamed: IC24.4 (I0), IC30.13 (I), IC35.8 (O)
REG-LD-ID0: IC35.1 (I0); also elsewhere on the board
REG-LD-ID1: IC35.2 (I1); also elsewhere on the board
REG-LD-ID2: IC24.12 (I0); also elsewhere on the board
REG-LD-ID3: IC24.13 (I1); also elsewhere on the board
VCC: IC12.14 (VCC), IC24.14 (VCC), IC25.20 (VCC), IC26.20 (VCC), IC27.20 (VCC), IC28.20 (VCC), IC29.14 (VCC), IC30.14 (VCC), IC35.14 (VCC); also elsewhere on the board

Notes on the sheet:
add SR FLip Flop clear with ucode counter reset
